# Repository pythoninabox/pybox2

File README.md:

# python in a box (pybox)

## circuitpython installation

1. Mount pybox via usb
2. Copy circuipython uf2 file inside `/circuitpython` folder
3. Copy all content inside `/lib` into `/CIRCUITPY/lib`, alternatively use `install.sh` script (only for linux)

## Upgrade pybox package

Copy `src/pybox` into `CIRCUITPY/lib`

## Simple Usage

There are six modules in this package:
1. **led**, to manage a single led (internalor external, as a part of ring led strip)
2. **button**, to manage the button
3. **pot**, to manage the potentiometer
4. **ring**, to manage the led ring
5. **tone**, to manage tone production, and send them to the internal speaker

### led module

#### example:

```py
from pybox.led import LED

# choose external led
led = LED('external') 

# led on
led.on()

#led off
led.off()
```

#### api

```py
# constructor
led = pybox.led.LED(target='internal')

# on and off 
led.on()
led.off()

# toggle: off if led is on and viceversa
led.toggle()

# write a digital value on led (0 or 1) an color it
led.write(1, GREEN)
led.write(0)
```

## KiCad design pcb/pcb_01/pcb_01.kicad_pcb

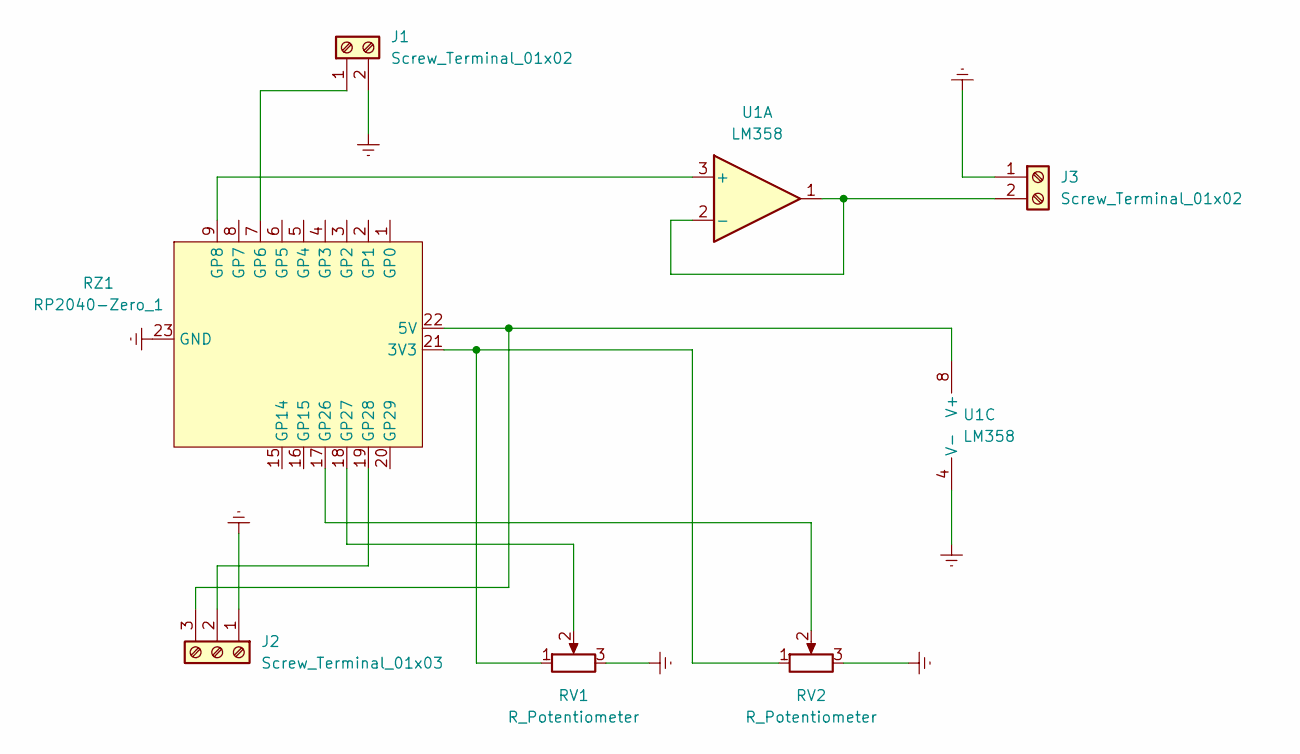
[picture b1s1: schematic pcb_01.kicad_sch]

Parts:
J1, J3: Screw_Terminal_01x02; TerminalBlock_bornier-2_P5.08mm
J2: Screw_Terminal_01x03; TerminalBlock_bornier-3_P5.08mm
RV1, RV2: R_Potentiometer; Potentiometer_Alps_RK097_Single_Horizontal
RZ1: RP2040-Zero_1; RP2040-Zero_copia
U1: LM358

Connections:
Earth: J1.2, J2.1, J3.1, RV1.3, RV2.3, RZ1.23 (GND), U1.4 (V-)
unnamed: J1.1, RZ1.7 (GP6)
unnamed: J2.3, RZ1.22 (5V), U1.8 (V+)
unnamed: J3.2, U1.1, U1.2 (-)
unnamed: RV1.1, RV2.1, RZ1.21 (3V3)
unnamed: RV1.2, RZ1.18 (GP27)
unnamed: RV2.2, RZ1.17 (GP26)
unnamed: RZ1.9 (GP8), U1.3 (+)
unnamed: J2.2, RZ1.19 (GP28)

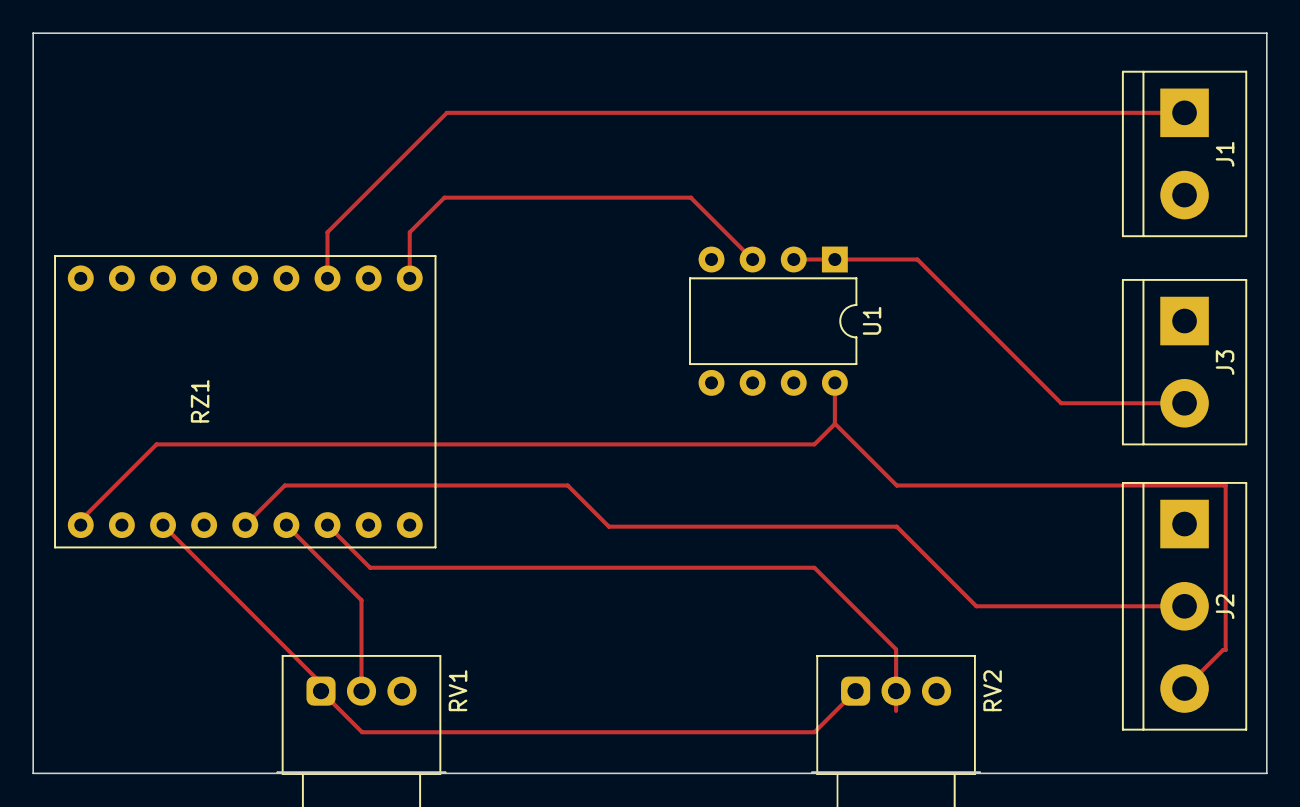
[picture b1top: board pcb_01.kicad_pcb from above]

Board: 2 copper layers, 76.2 x 45.7 mm, 7 parts (0 on the bottom side), 9 nets.

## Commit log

2023-02-27 clean main
2023-02-27 ADD: button && pot
2023-03-04 ADD: various funcs to manage color and pixels
2023-03-05 FIX: __setitem__() && set(), REMOVED: sets()
2023-03-05 update GP pin
2023-03-12 update layout
2023-03-17 upate doc
2023-03-26 update doc
2023-03-29 test keypad on button
2023-04-02 ADD: SIMPLEBUTTON class && REFACTOR: BUTTON class with keypad module
2023-04-02 ADD: clean doc
2023-04-02 REFACTOR FILE SYSTEM && ADD: press_time property (BUTTON class)
2023-04-03 Deployed 04f45e7 with MkDocs version: 1.4.2
2023-04-07 update docs and fill() method, full_color property
2023-04-07 format && ring doc
2023-04-09 Deployed 116ae85 with MkDocs version: 1.4.2
2023-04-09 update doc of ring and button
2023-04-09 clean doc
2023-04-10 update doc on update()
2023-04-10 ADD: mpy generator
2023-04-10 add mpy package format
2023-04-10 FIX: update() -> call callback function only if it exists
2023-04-10 FIX: add get_pixel_color()
2023-04-10 RENAMED: old RING in new ARING && ADD: PIXEL && RING classes
2023-04-10 ADD: deinit() on RING class
2023-04-10 new version
2023-04-11 Deployed 3046127 with MkDocs version: 1.4.2
2023-04-11 fix doc
2023-04-11 Deployed 9fb5727 with MkDocs version: 1.4.2
2023-04-11 ADD: __repr__() in PIXEL && RING
2023-04-11 Deployed 72f1b18 with MkDocs version: 1.4.2
2023-04-11 Deployed 679bf92 with MkDocs version: 1.4.2
2023-04-11 update doc links
2023-04-11 Deployed 4e9ee7f with MkDocs version: 1.4.2
2023-04-12 Deployed b869890 with MkDocs version: 1.4.2
2023-04-14 Deployed 87f4f72 with MkDocs version: 1.4.2
2023-04-14 Deployed 538b52d with MkDocs version: 1.4.2
2023-04-14 add tutorial ring
2023-04-14 Deployed 4ad62b9 with MkDocs version: 1.4.2
2023-04-14 Deployed 00756aa with MkDocs version: 1.4.2
2023-04-14 Deployed 67da66d with MkDocs version: 1.4.2
2023-04-14 Deployed be34a46 with MkDocs version: 1.4.2
2023-04-14 Deployed 779150b with MkDocs version: 1.4.2
2023-04-16 Upload image semaforo
2023-04-16 Deployed c9ce09a with MkDocs version: 1.4.2
2023-04-16 Deployed 2cdd93b with MkDocs version: 1.4.2
2023-04-16 Deployed a2a511c with MkDocs version: 1.4.2
2023-04-16 Deployed 64a7b6f with MkDocs version: 1.4.2
2023-04-17 update docs
2023-04-17 Deployed 39be70d with MkDocs version: 1.4.2
2023-04-24 update pcb
2023-05-20 add 'order' in constructor
2023-05-21 update test 1 for web_updater
2023-05-24 add pin_class and value method
2023-05-25 update RGB order on led
2023-06-05 Deployed 6dccaa4 with MkDocs version: 1.4.2
2023-06-05 Deployed 0be64e1 with MkDocs version: 1.4.2
2023-06-05 Deployed 8a10d4d with MkDocs version: 1.4.2
2023-06-05 Deployed fc3dbe7 with MkDocs version: 1.4.2
2023-06-05 Deployed e989d4e with MkDocs version: 1.4.2
2023-06-05 Deployed 72160d8 with MkDocs version: 1.4.2
2023-06-05 Deployed 27f24ee with MkDocs version: 1.4.2
2023-07-04 Deployed 6c272cb with MkDocs version: 1.4.3
2023-07-04 Deployed 40e2f55 with MkDocs version: 1.4.3
2023-07-04 Deployed d83b44f with MkDocs version: 1.4.3
2023-07-04 Deployed 653d5e3 with MkDocs version: 1.4.3
2023-11-23 Deployed 34857c5 with MkDocs version: 1.5.3
2023-11-23 Deployed 6fb7378 with MkDocs version: 1.5.3
2024-05-12 FIX: add pin to button and simplebutton
2024-05-12 update release
